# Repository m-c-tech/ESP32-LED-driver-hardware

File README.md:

# ESP32-LED-driver-hardware
A board to drive WRGB and addressable LEDs using a NodeMCU-32S ESP32 WiFi microcontroller development board.  

## Goals:
The goal for this project was to make an ESPHOME and Home Assistant compatible LED strip controller.  
Price is an important factor as well as ease of use and flexibility in its applications.  
[ESPHome](https://esphome.io/) is a software tool that can generate code for the ESP32 microcontrollers by using simple configuration files and [Home Assistant](https://www.home-assistant.io/) has a graphical interface to set up automations.  
This gives great flexibility with over-the-air updates and easy to understand setup.  
The ESP32 microcontroller is highly flexible with WiFi and bluetooth along with many GPIOs, ADCs, touch sensors, etc.  
Development boards for the ESP32 can be gotten for very cheap from various online sellers, pay close attention to the dev board pinouts as they can vary.  
This PCB design incorporates multiple resistor configurations to allow for differing types of LEDs to be driven, common anode, SPI, one wire.

## Software and costs:  
PCB design done in KICAD 6.0  
Mechanical enclosure design done in Autodesk Fusion 360.  
The bill of materials comes to roughly 20.70AUD per unit at quantaties of 20.  
This includes the ESP32 dev board ($6.75), components from digi-key ($7.80), PCBs from fab house ($2.27), 3D printer plastic ($1.60), plus a few other items.  

## Enclosure:  
Designed for 3D printing.  
Dimensions - (L) 56.6mm * (W) 56.6mm * (D) 26mm  
The enclosure needs a M3 heated nut-sert to be put in the lid and a countersunk M3 machine screw.  

## Power:  
Input power can be 5V to 12V up to 5A current.  
Input connector is a 2.1mm ID, 5.5mm OD, 9.5mm long barrel jack plug.  

## Pinouts:  
Pinout used for common anode RGBW 5/12V LEDs:  
VDD  - Power +ve  
IO19 - White  
IO18 - Red  
IO17 - Green  
IO16 - Blue  
GND	 - Unused  

Hardware changes for driving addressable LEDs:  
Remove 0R resistors from R1-R4.  
Place 0R resistors on R5-R7.  

Pinout for up to 4 strings of one wire addressable LEDs:  
VDD  - Power +ve (ensure your power supply is correct for your LED voltage)  
IO19 - LED data 1  
IO18 - LED data 2  
IO17 - LED data 3  
IO16 - LED data 4  
GND	 - GND  

Pinout used for 2 strings of SPI addressable LEDs:  
VDD  - Power +ve (ensure your power supply is correct for your LED voltage)  
IO19 - LED data 0  
IO18 - LED clock 0  
IO17 - LED data 1  
IO16 - LED clock 1  
GND	 - GND

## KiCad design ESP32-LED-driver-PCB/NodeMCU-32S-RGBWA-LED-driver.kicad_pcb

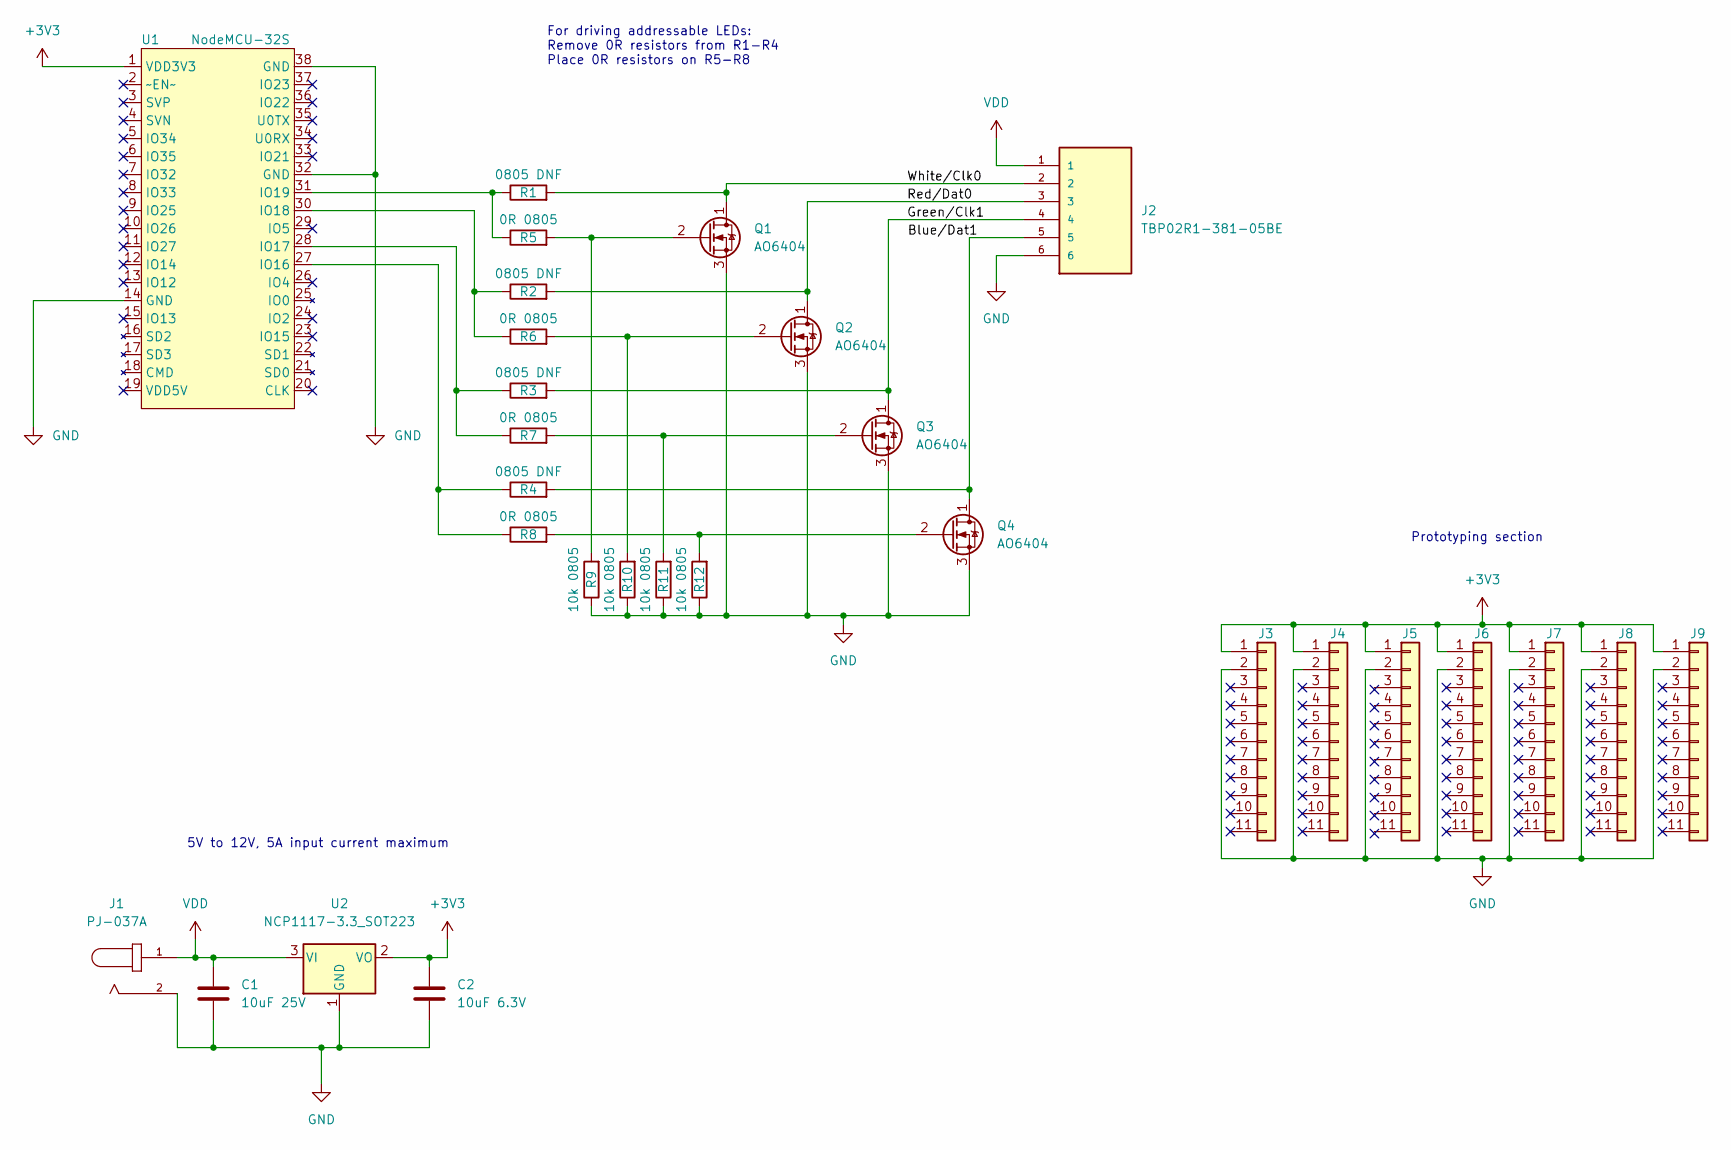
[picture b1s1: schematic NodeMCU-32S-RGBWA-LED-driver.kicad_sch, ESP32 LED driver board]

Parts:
C1: 10uF 25V; C_0805_2012Metric
C2: 10uF 6.3V; C_0603_1608Metric
J1: PJ-037A; CUI_PJ-037A
J2: TBP02R1-381-05BE; CUI_TBP02R1-381-06BE
J3, J4, J5, J6, J7, J8, J9: Conn_01x11; PinHeader_1x11_P2.54mm_Vertical
Q1, Q2, Q3, Q4: AO6404
R1, R2, R3, R4: 0805 DNF; R_0805_2012Metric
R5, R6, R7, R8: 0R 0805; R_0805_2012Metric
R9, R10, R11, R12: 10k 0805; R_0805_2012Metric
U1: NodeMCU-32S
U2: NCP1117-3.3_SOT223; SOT-223-3_TabPin2

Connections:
+3V3: C2.1, J3.1, J4.1, J5.1, J6.1, J7.1, J8.1, J9.1, U1.1 (VDD3V3), U2.2 (VO)
/Blue/Dat1: J2.5, Q4.1 (D), R4.2
/Green/Clk1: J2.4, Q3.1 (D), R3.2
/Red/Dat0: J2.3, Q2.1 (D), R2.2
/White/Clk0: J2.2, Q1.1 (D), R1.2
GND: C1.2, C2.2, J1.2, J2.6, J3.2, J4.2, J5.2, J6.2, J7.2, J8.2, J9.2, Q1.3 (S), Q2.3 (S), Q3.3 (S), Q4.3 (S), R9.1, R10.1, R11.1, R12.1, U1.14 (GND), U1.32 (GND), U1.38 (GND), U2.1 (GND)
unnamed: Q1.2 (G), R5.2, R9.2
unnamed: Q2.2 (G), R6.2, R10.2
unnamed: Q3.2 (G), R7.2, R11.2
unnamed: Q4.2 (G), R8.2, R12.2
unnamed: R4.1, R8.1, U1.27 (IO16)
unnamed: R3.1, R7.1, U1.28 (IO17)
unnamed: R2.1, R6.1, U1.30 (IO18)
unnamed: R1.1, R5.1, U1.31 (IO19)
VDD: C1.1, J1.1, J2.1, U2.3 (VI)

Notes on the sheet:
For driving addressable LEDs: Remove 0R resistors from R1-R4 Place 0R resistors on R5-R8
5V to 12V, 5A input current maximum
Prototyping section

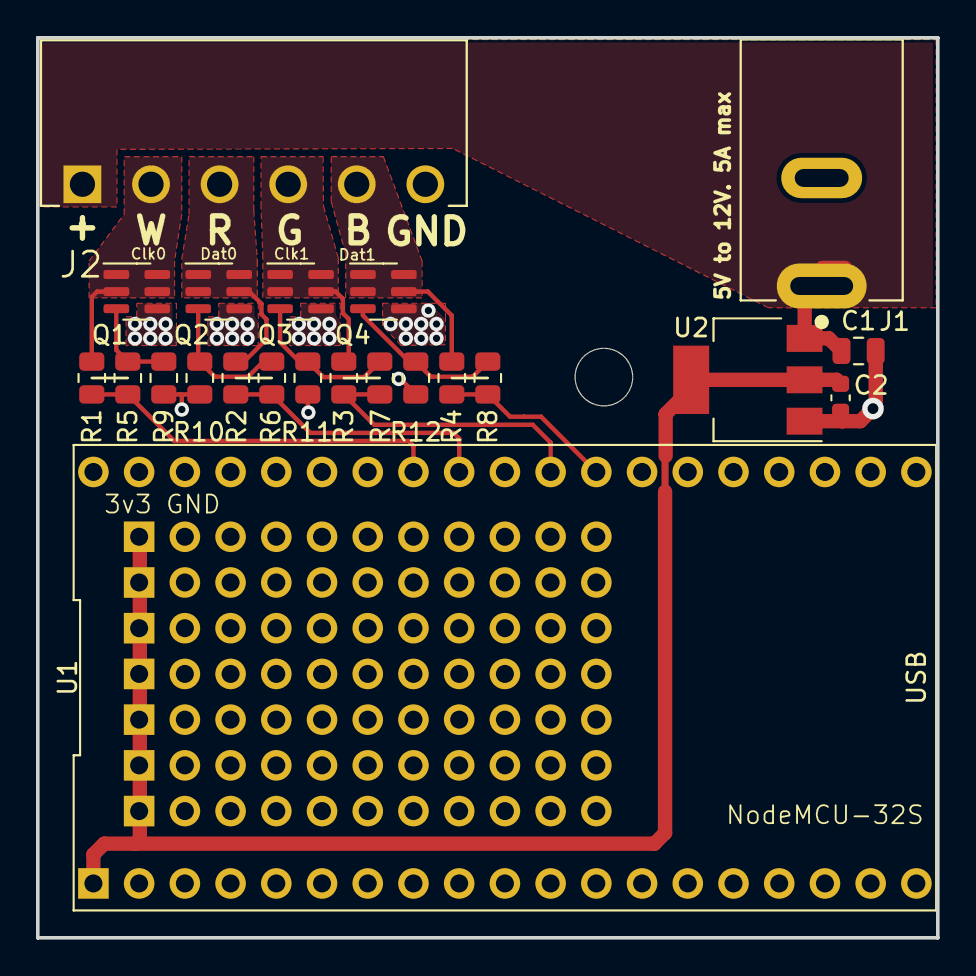
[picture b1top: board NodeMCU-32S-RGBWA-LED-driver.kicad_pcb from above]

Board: 2 copper layers, 50.0 x 50.0 mm, 29 parts (0 on the bottom side), 15 nets.

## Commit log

2022-01-02 First commit of all files
    Hardware layout has gone through a few revisions already. Should be okay to send to the PCB factory
2022-01-02 Created README
    Read it, it's a README
2022-01-02 Re-organising folders
    Re-organising folders
2022-01-02 Adding images
    Images for README
2022-01-02 Fixed README image link
2022-01-02 Added Fusion 360 project file
2022-01-02 Clean up
2022-01-02 Added pinout descriptions
2022-01-02 Project description
2022-01-02 Updated silkscreen
2022-01-02 Updated to 6 pin connector
    Moved to 6 pin connector to get more addressable outputs with a dedicated ground pin.
2022-01-03 Added prototyping area
    Added prototyping area to allow for extra sensors.
    Updated some silkscreen
2022-01-03 Updated enclosure for 6 pin device
2022-01-06 Updated screw clearances and heat-sert dimensions
2022-01-06 Fixed last commit
2022-01-16 💡 Add LED Tester Firmware
2022-07-02 Added more example firmware
    Added examples of addressable and RGBW control using FastLED library and RGBW with no libraries.
2023-05-18 Updated documentation
    Schematics pdf and README referenced an older version of the schematics. Updated to remove these references.
2023-05-23 Modified enclosure
    Fixed an incorrect heat insert diameter
    Updated the fusion 360 project
2023-05-24 Updated enclosure
    Enclosure updated with better PCB supports and flexible buttons
2023-05-25 Updated enclosure buttons
    Made the buttons easier to push
